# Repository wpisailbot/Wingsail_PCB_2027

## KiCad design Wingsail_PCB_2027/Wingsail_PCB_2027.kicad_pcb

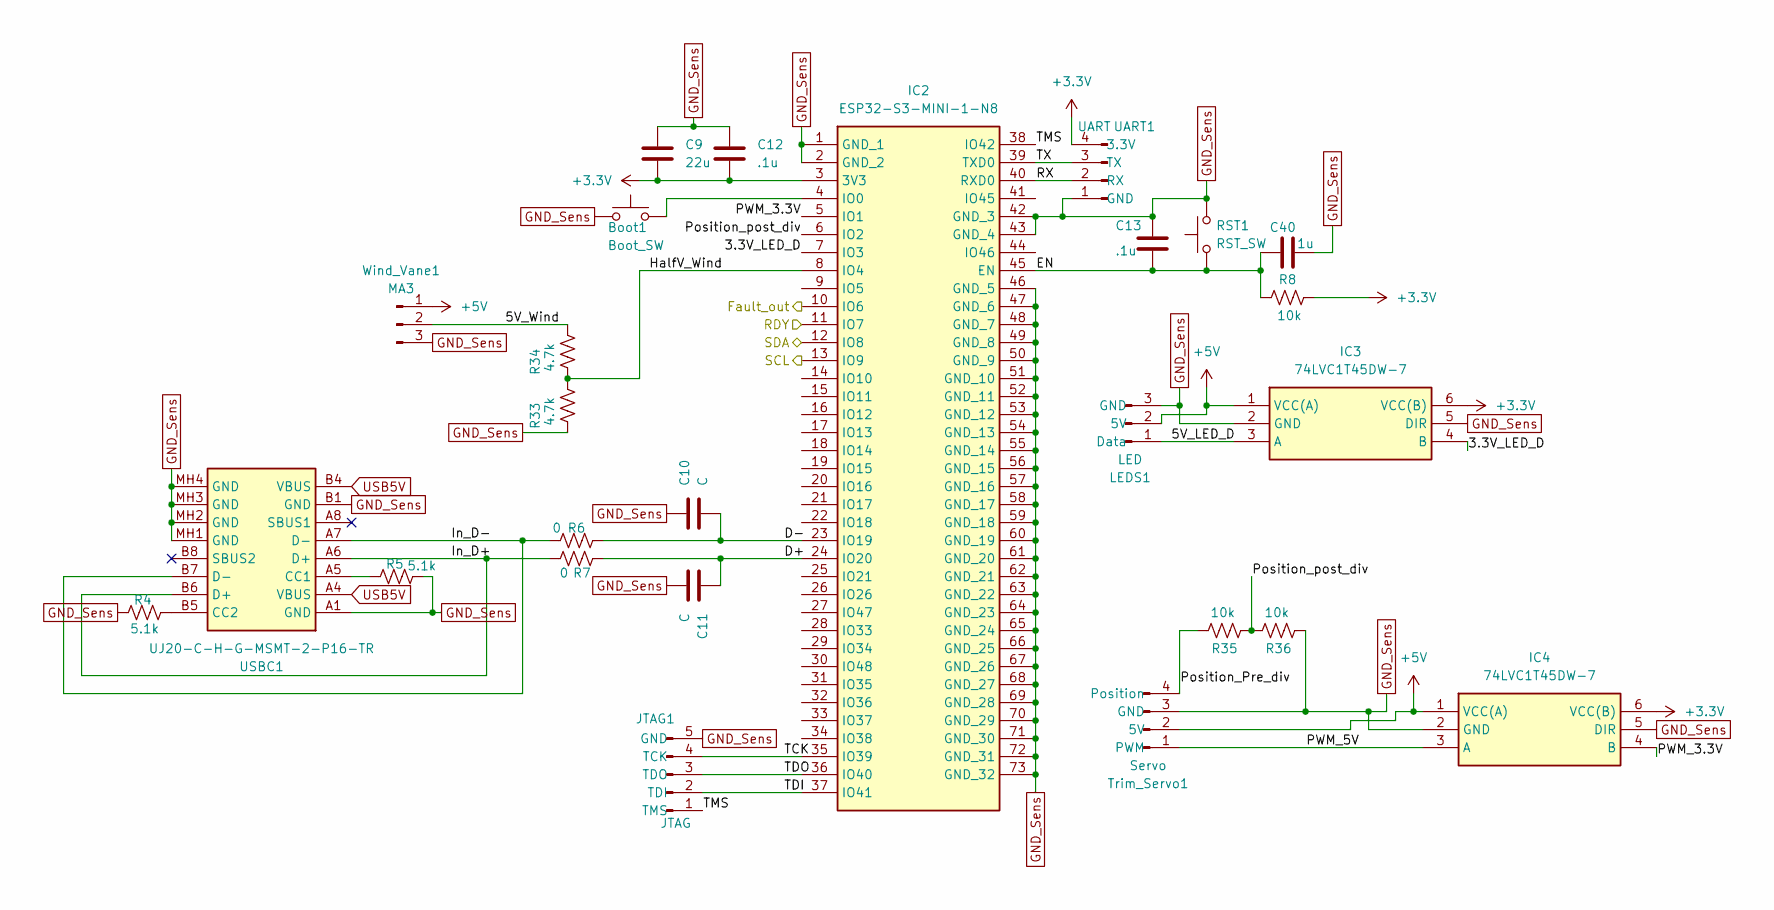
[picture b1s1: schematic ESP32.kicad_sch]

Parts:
Boot1: Boot_SW; PTS636SM43LFS; Part# 1825910-7; Digikey# 450-1804-ND
C9: 22u; C_0805_2012Metric_Pad1.18x1.45mm_HandSolder; Part# CL21A226KQCLRNC; Digikey# 1276-6687-1-ND
C10, C11: C; C_0805_2012Metric_Pad1.18x1.45mm_HandSolder
C12, C13: .1u; C_0805_2012Metric_Pad1.18x1.45mm_HandSolder; Part# CL21B104KBCNNNC; Digikey# 1276-1003-1-ND
C40: 1u; C_0805_2012Metric_Pad1.18x1.45mm_HandSolder; Part# TMK212BBJ106KG-T; Digikey# 587-2985-1-ND
IC2: ESP32-S3-MINI-1-N8; ESP32S3MINI1N8; Manufacturer_Part_Number ESP32-S3-MINI-1-N8; Mouser Part Number 356-ESP32-S3-MINI1N8
IC3, IC4: 74LVC1T45DW-7; SOT65P210X110-6N; Manufacturer_Part_Number 74LVC1T45DW-7; Mouser Part Number 621-74LVC1T45DW-7
JTAG1: JTAG; PinSocket_1x05_P2.54mm_Vertical
LEDS1: LED; JST_XH_B3B-XH-A_1x03_P2.50mm_Vertical
R4, R5: 5.1k; R_0805_2012Metric_Pad1.20x1.40mm_HandSolder; Part# RK73H2ATTD5101F; Digikey# 2019-RK73H2ATTD5101FCT-ND
R6, R7: 0; R_0805_2012Metric_Pad1.20x1.40mm_HandSolder; Part# RMCF0805ZT0R00; Digikey# RMCF0805ZT0R00CT-ND
R8, R35, R36: 10k; R_0805_2012Metric_Pad1.20x1.40mm_HandSolder; Part# RK73H2ATTD1002F; Digikey# 2019-RK73H2ATTD1002FCT-ND
R33, R34: 4.7k; R_0805_2012Metric_Pad1.20x1.40mm_HandSolder; Part# RK73H2ATTD4701F; Digikey# 2019-RK73H2ATTD4701FCT-ND
RST1: RST_SW; PTS636SM43LFS; Part# 1825910-7; Digikey# 450-1804-ND
Trim_Servo1: Servo; JST_XH_B4B-XH-A_1x04_P2.50mm_Vertical
UART1: UART; PinSocket_1x04_P2.54mm_Vertical
USBC1: UJ20-C-H-G-MSMT-2-P16-TR; UJ20CHGMSMT2P16TR; Manufacturer_Part_Number UJ20-C-H-G-MSMT-2-P16-TR; Mouser Part Number 179-UJ20CHGMSMT2P16T
Wind_Vane1: MA3; JST_XH_B3B-XH-A_1x03_P2.50mm_Vertical

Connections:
+3.3V: C9.1, C12.2, IC2.3 (3V3), IC3.6 (VCC(B)), IC4.6 (VCC(B)), R8.2, UART1.4 (3.3V); also elsewhere on the board
+5V: IC3.1 (VCC(A)), IC4.1 (VCC(A)), LEDS1.2 (5V), Trim_Servo1.2 (5V), Wind_Vane1.1; also elsewhere on the board
/BMS/Fault_in: IC2.10 (IO6); also elsewhere on the board
/BMS/RDY: IC2.11 (IO7); also elsewhere on the board
/BMS/SCL: IC2.13 (IO9); also elsewhere on the board
/BMS/SDA: IC2.12 (IO8); also elsewhere on the board
/ESP32/3.3V_LED_D: IC2.7 (IO3), IC3.4 (B)
/ESP32/5V_LED_D: IC3.3 (A), LEDS1.1 (Data)
/ESP32/5V_Wind: R34.2, Wind_Vane1.2
/ESP32/D+: C11.1, IC2.24 (IO20), R7.2
/ESP32/D-: C10.2, IC2.23 (IO19), R6.2
/ESP32/EN: C13.2, C40.1, IC2.45 (EN), R8.1, RST1.1
/ESP32/HalfV_Wind: IC2.8 (IO4), R33.2, R34.1
/ESP32/In_D+: R7.1, USBC1.A6 (D+), USBC1.B6 (D+)
/ESP32/In_D-: R6.1, USBC1.A7 (D-), USBC1.B7 (D-)
/ESP32/PWM_3.3V: IC2.5 (IO1), IC4.4 (B)
/ESP32/PWM_5V: IC4.3 (A), Trim_Servo1.1 (PWM)
/ESP32/Position_Pre_div: R35.2, Trim_Servo1.4 (Position)
/ESP32/Position_post_div: IC2.6 (IO2), R35.1, R36.2
/ESP32/RX: IC2.40 (RXD0), UART1.2 (RX)
/ESP32/TCK: IC2.35 (IO39), JTAG1.4 (TCK)
/ESP32/TDI: IC2.37 (IO41), JTAG1.2 (TDI)
/ESP32/TDO: IC2.36 (IO40), JTAG1.3 (TDO)
/ESP32/TMS: IC2.38 (IO42), JTAG1.1 (TMS)
/ESP32/TX: IC2.39 (TXD0), UART1.3 (TX)
GND_Sens: Boot1.1, C9.2, C10.1, C11.2, C12.1, C13.1, C40.2, IC2.1 (GND_1), IC2.2 (GND_2), IC2.42 (GND_3), IC2.43 (GND_4), IC2.46 (GND_5), IC2.47 (GND_6), IC2.48 (GND_7), IC2.49 (GND_8), IC2.50 (GND_9), IC2.51 (GND_10), IC2.52 (GND_11), IC2.53 (GND_12), IC2.54 (GND_13), IC2.55 (GND_14), IC2.56 (GND_15), IC2.57 (GND_16), IC2.58 (GND_17), IC2.59 (GND_18), IC2.60 (GND_19), IC2.61 (GND_20), IC2.62 (GND_21), IC2.63 (GND_22), IC2.64 (GND_23), IC2.65 (GND_24), IC2.66 (GND_25), IC2.67 (GND_26), IC2.68 (GND_27), IC2.69 (GND_28), IC2.70 (GND_29), IC2.71 (GND_30), IC2.72 (GND_31), IC2.73 (GND_32), IC3.2 (GND), IC3.5 (DIR), IC4.2 (GND), IC4.5 (DIR), JTAG1.5 (GND), LEDS1.3 (GND), R4.1, R5.2, R33.1, R36.1, RST1.2, Trim_Servo1.3 (GND), UART1.1 (GND), USBC1.A1 (GND), USBC1.B1 (GND), USBC1.MH1 (GND), USBC1.MH2 (GND), USBC1.MH3 (GND), USBC1.MH4 (GND), Wind_Vane1.3; also elsewhere on the board
unnamed: Boot1.2, IC2.4 (IO0)
unnamed: R5.1, USBC1.A5 (CC1)
unnamed: R4.2, USBC1.B5 (CC2)
USB5V: USBC1.A4 (VBUS), USBC1.B4 (VBUS); also elsewhere on the board

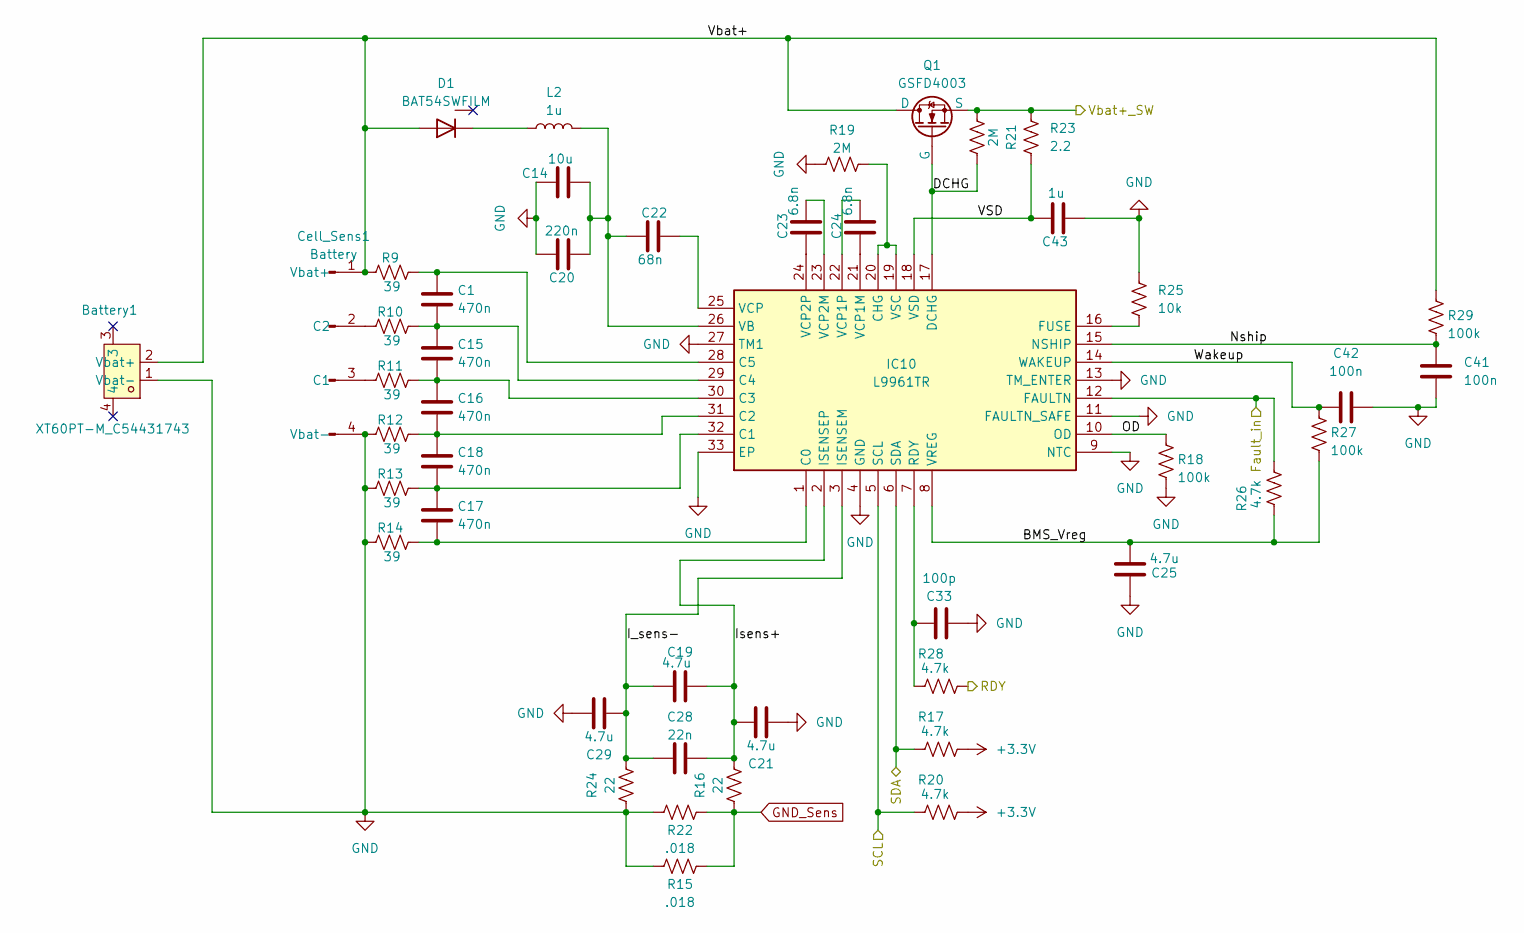
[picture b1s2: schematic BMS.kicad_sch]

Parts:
Battery1: XT60PT-M_C54431743; CONN-SMD_XT60PT-M_C9900188634; MPN XT60PT-M; LCSC Part C54431743
C1, C15, C16, C17, C18: 470n; C_0805_2012Metric_Pad1.18x1.45mm_HandSolder; Part# CL21B474KAFNNNG; Digikey# 1276-6480-1-ND
C14: 10u; C_0805_2012Metric_Pad1.18x1.45mm_HandSolder; Part# TMK212BBJ106KG-T; Digikey# 587-2985-1-ND
C19, C21, C25, C29: 4.7u; C_0805_2012Metric_Pad1.18x1.45mm_HandSolder; Part# GRM219R6YA475KA73D; Digikey# 490-7208-1-ND
C20: 220n; C_0805_2012Metric_Pad1.18x1.45mm_HandSolder; Part# CL21B224KBFNNNF; Digikey# 1276-CL21B224KBFNNNFCT-ND
C22: 68n; C_0805_2012Metric_Pad1.18x1.45mm_HandSolder; Part# GMC21X7R683K50NT; Digikey# 4713-GMC21X7R683K50NTCT-ND
C23, C24: 6.8n; C_0805_2012Metric_Pad1.18x1.45mm_HandSolder; Part# 0805B682K500CT; Digikey# 1292-1587-1-ND
C28: 22n; C_0805_2012Metric_Pad1.18x1.45mm_HandSolder; Part# CL21B223JBANNNC; Digikey# 1276-1826-1-ND
C33: 100p; C_0805_2012Metric_Pad1.18x1.45mm_HandSolder; Part# CL21C101JCANNNC; Digikey# 1276-1261-1-ND
C41, C42: 100n; C_0805_2012Metric_Pad1.18x1.45mm_HandSolder; Part# CL21B104KBCNNNC; Digikey# 1276-1003-1-ND
C43: 1u; C_0805_2012Metric_Pad1.18x1.45mm_HandSolder; Part# TMK212BBJ106KG-T; Digikey# 587-2985-1-ND
Cell_Sens1: Battery; JST_XH_S4B-XH-A_1x04_P2.50mm_Horizontal; Part# S4B-XH-A; Digikey# 455-2243-ND
D1: BAT54SWFILM; SOT-323_SC-70; Part# BAT54SWFILM; Digikey# 497-14153-1-ND
IC10: L9961TR; QFN50P500X500X100-33N-D; Manufacturer_Part_Number L9961TR; Digikey# 497-L9961TRCT-ND
L2: 1u; L_0805_2012Metric_Pad1.05x1.20mm_HandSolder; Part# MLZ2012N1R0LT000; Digikey# 445-6756-1-ND
Q1: GSFD4003; TO-252-GSFD4003; Part# GSFD4003; Digikey# 4786-GSFD4003CT-ND
R9, R10, R11, R12, R13, R14: 39; R_0805_2012Metric_Pad1.20x1.40mm_HandSolder; Power Rating Min 1/8 W; Part# RK73H2ATTD39R0F; Digikey# 2019-RK73H2ATTD39R0FCT-ND
R15, R22: .018; WSHP2818R0180FEA; Part# WSHP2818R0180FEA; Digikey# 541-WSHP2818R0180FEACT-ND
R16, R24: 22; R_0805_2012Metric_Pad1.20x1.40mm_HandSolder; Part# RK73H2ATTD22R0F; Digikey# 2019-RK73H2ATTD22R0FCT-ND
R17, R20, R26, R28: 4.7k; R_0805_2012Metric_Pad1.20x1.40mm_HandSolder; Part# RK73H2ATTD4701F; Digikey# 2019-RK73H2ATTD4701FCT-ND
R18, R27, R29: 100k; R_0805_2012Metric_Pad1.20x1.40mm_HandSolder; Part# RK73H2ATTD1003F; Digikey# 2019-RK73H2ATTD1003FCT-ND
R19, R21: 2M; R_0805_2012Metric_Pad1.20x1.40mm_HandSolder; Part# RK73H2ATTD2004F; Digikey# 2019-RK73H2ATTD2004FCT-ND
R23: 2.2; R_0805_2012Metric_Pad1.20x1.40mm_HandSolder; Part# RK73H2ATTD2R20F; Digikey# 2019-RK73H2ATTD2R20FCT-ND
R25: 10k; R_0805_2012Metric_Pad1.20x1.40mm_HandSolder; Part# RK73H2ATTD1002F; Digikey# 2019-RK73H2ATTD1002FCT-ND

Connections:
+3.3V: R17.2, R20.2; also elsewhere on the board
/BMS/BMS_Vreg: C25.1, IC10.8 (VREG), R26.1, R27.2
/BMS/DCHG: IC10.17 (DCHG), Q1.2 (G), R21.1
/BMS/Fault_in: IC10.12 (FAULTN), R26.2; also elsewhere on the board
/BMS/I_sens-: C19.2, C28.1, C29.1, IC10.3 (ISENSEM), R24.1
/BMS/Isens+: C19.1, C21.2, C28.2, IC10.2 (ISENSEP), R16.1
/BMS/Nship: C41.1, IC10.15 (NSHIP), R29.2
/BMS/OD: IC10.10 (OD), R18.1
/BMS/RDY: R28.2; also elsewhere on the board
/BMS/SCL: IC10.5 (SCL), R20.1; also elsewhere on the board
/BMS/SDA: IC10.6 (SDA), R17.1; also elsewhere on the board
/BMS/VSD: C43.1, IC10.18 (VSD), R23.2
/BMS/Vbat+: Battery1.2 (Vbat+), Cell_Sens1.1 (Vbat+), D1.1 (A), Q1.1 (D), R9.1, R29.1
/BMS/Vbat+_SW: Q1.3 (S), R21.2, R23.1; also elsewhere on the board
/BMS/Wakeup: C42.2, IC10.14 (WAKEUP), R27.1
GND: Battery1.1 (Vbat-), C14.1, C20.1, C21.1, C25.2, C29.2, C33.1, C41.2, C42.1, C43.2, Cell_Sens1.4 (Vbat-), IC10.4 (GND), IC10.9 (NTC), IC10.11 (FAULTN_SAFE), IC10.13 (TM_ENTER), IC10.27 (TM1), IC10.33 (EP), R12.1, R13.1, R14.1, R15.2, R18.2, R19.2, R22.2, R24.2, R25.1
GND_Sens: R15.1, R16.2, R22.1; also elsewhere on the board
unnamed: Cell_Sens1.3 (C1), R11.1
unnamed: Cell_Sens1.2 (C2), R10.1
unnamed: D1.2 (K), L2.1
unnamed: C17.1, IC10.1 (C0), R14.2
unnamed: C17.2, C18.1, IC10.32 (C1), R13.2
unnamed: C16.1, C18.2, IC10.31 (C2), R12.2
unnamed: C15.1, C16.2, IC10.30 (C3), R11.2
unnamed: C1.1, C15.2, IC10.29 (C4), R10.2
unnamed: C1.2, IC10.28 (C5), R9.2
unnamed: IC10.19 (VSC), IC10.20 (CHG), R19.1
unnamed: IC10.16 (FUSE), R25.2
unnamed: C33.2, IC10.7 (RDY), R28.1
unnamed: C14.2, C20.2, C22.2, IC10.26 (VB), L2.2
unnamed: C24.2, IC10.21 (VCP1M)
unnamed: C24.1, IC10.22 (VCP1P)
unnamed: C23.1, IC10.23 (VCP2M)
unnamed: C23.2, IC10.24 (VCP2P)
unnamed: C22.1, IC10.25 (VCP)

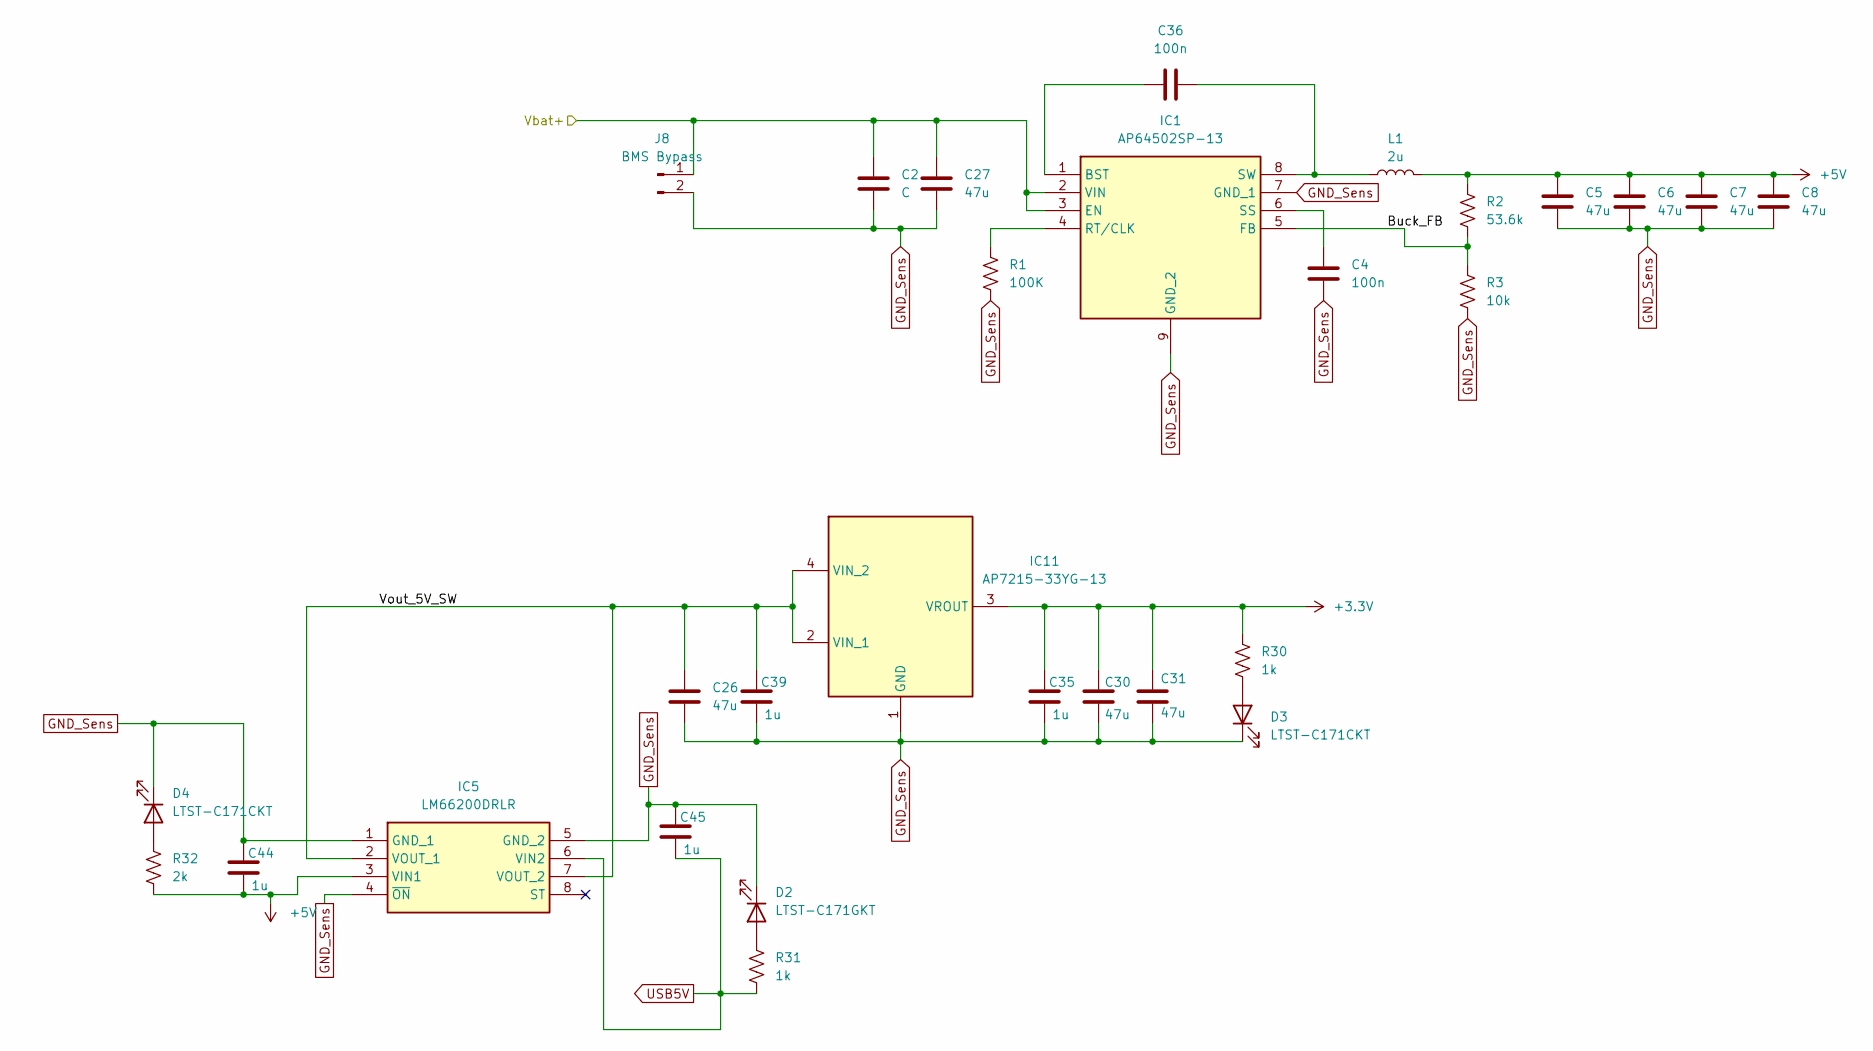
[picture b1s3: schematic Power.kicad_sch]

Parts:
C2: C; C_0805_2012Metric_Pad1.18x1.45mm_HandSolder
C4, C36: 100n; C_0805_2012Metric_Pad1.18x1.45mm_HandSolder; Part# CL21B104KBCNNNC; Digikey# 1276-1003-1-ND
C5, C6, C7, C8, C26, C27, C30, C31: 47u; C_0805_2012Metric_Pad1.18x1.45mm_HandSolder; Part# GRM21BR61A476ME15K; Digikey# 490-GRM21BR61A476ME15KCT-ND
C35, C39, C44, C45: 1u; C_0805_2012Metric_Pad1.18x1.45mm_HandSolder; Part# TMK212BBJ106KG-T; Digikey# 587-2985-1-ND
D2: LTST-C171GKT; LED_0805_2012Metric_Pad1.15x1.40mm_HandSolder
D3, D4: LTST-C171CKT; LED_0805_2012Metric_Pad1.15x1.40mm_HandSolder
IC1: AP64502SP-13; SOIC127P600X163-9N; Manufacturer_Part_Number AP64502SP-13; Mouser Part Number 621-AP64502SP-13
IC5: LM66200DRLR; SOTFL50P160X60-8N; Manufacturer_Part_Number LM66200DRLR; Mouser Part Number 595-LM66200DRLR
IC11: AP7215-33YG-13; AZ7042RTRG1; Manufacturer_Part_Number AP7215-33YG-13; Mouser Part Number 621-AP7215-33YG-13
J8: BMS Bypass; PinHeader_1x02_P2.54mm_Vertical
L1: 2u; IND-SMD_L7.1-W6.6; Part# CSBX0650-2R0M; Digikey# 4044-CSBX0650-2R0MCT-ND
R1: 100K; R_0805_2012Metric_Pad1.20x1.40mm_HandSolder; Part# RK73H2ATTD1003F; Digikey# 2019-RK73H2ATTD1003FCT-ND
R2: 53.6k; R_0805_2012Metric_Pad1.20x1.40mm_HandSolder; Part# RK73H2ATTD5362F; Digikey# 2019-RK73H2ATTD5362FCT-ND
R3: 10k; R_0805_2012Metric_Pad1.20x1.40mm_HandSolder; Part# RK73H2ATTD1002F; Digikey# 2019-RK73H2ATTD1002FCT-ND
R30, R31: 1k; R_0805_2012Metric_Pad1.20x1.40mm_HandSolder; Part# RK73H2ATTD1001F; Digikey# 2019-RK73H2ATTD1001FCT-ND
R32: 2k; R_0805_2012Metric_Pad1.20x1.40mm_HandSolder; Part# RK73H2ATTD2001F; Digikey# 2019-RK73H2ATTD2001FCT-ND

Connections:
+3.3V: C30.1, C31.1, C35.1, IC11.3 (VROUT), R30.1; also elsewhere on the board
+5V: C5.1, C6.1, C7.1, C8.1, C44.2, IC5.3 (VIN1), L1.2, R2.1, R32.2; also elsewhere on the board
/BMS/Vbat+_SW: C2.1, C27.1, IC1.2 (VIN), IC1.3 (EN), J8.1; also elsewhere on the board
/Power/Buck_FB: IC1.5 (FB), R2.2, R3.1
/Power/Vout_5V_SW: C26.1, C39.1, IC5.2 (VOUT_1), IC5.7 (VOUT_2), IC11.2 (VIN_1), IC11.4 (VIN_2)
GND_Sens: C2.2, C4.1, C5.2, C6.2, C7.2, C8.2, C26.2, C27.2, C30.2, C31.2, C35.2, C39.2, C44.1, C45.1, D2.1 (K), D3.1 (K), D4.1 (K), IC1.7 (GND_1), IC1.9 (GND_2), IC5.1 (GND_1), IC5.4 (~ON), IC5.5 (GND_2), IC11.1 (GND), J8.2, R1.2, R3.2; also elsewhere on the board
unnamed: D2.2 (A), R31.1
unnamed: D3.2 (A), R30.2
unnamed: D4.2 (A), R32.1
unnamed: C36.2, IC1.1 (BST)
unnamed: IC1.4 (RT/CLK), R1.1
unnamed: C4.2, IC1.6 (SS)
unnamed: C36.1, IC1.8 (SW), L1.1
USB5V: C45.2, IC5.6 (VIN2), R31.2; also elsewhere on the board

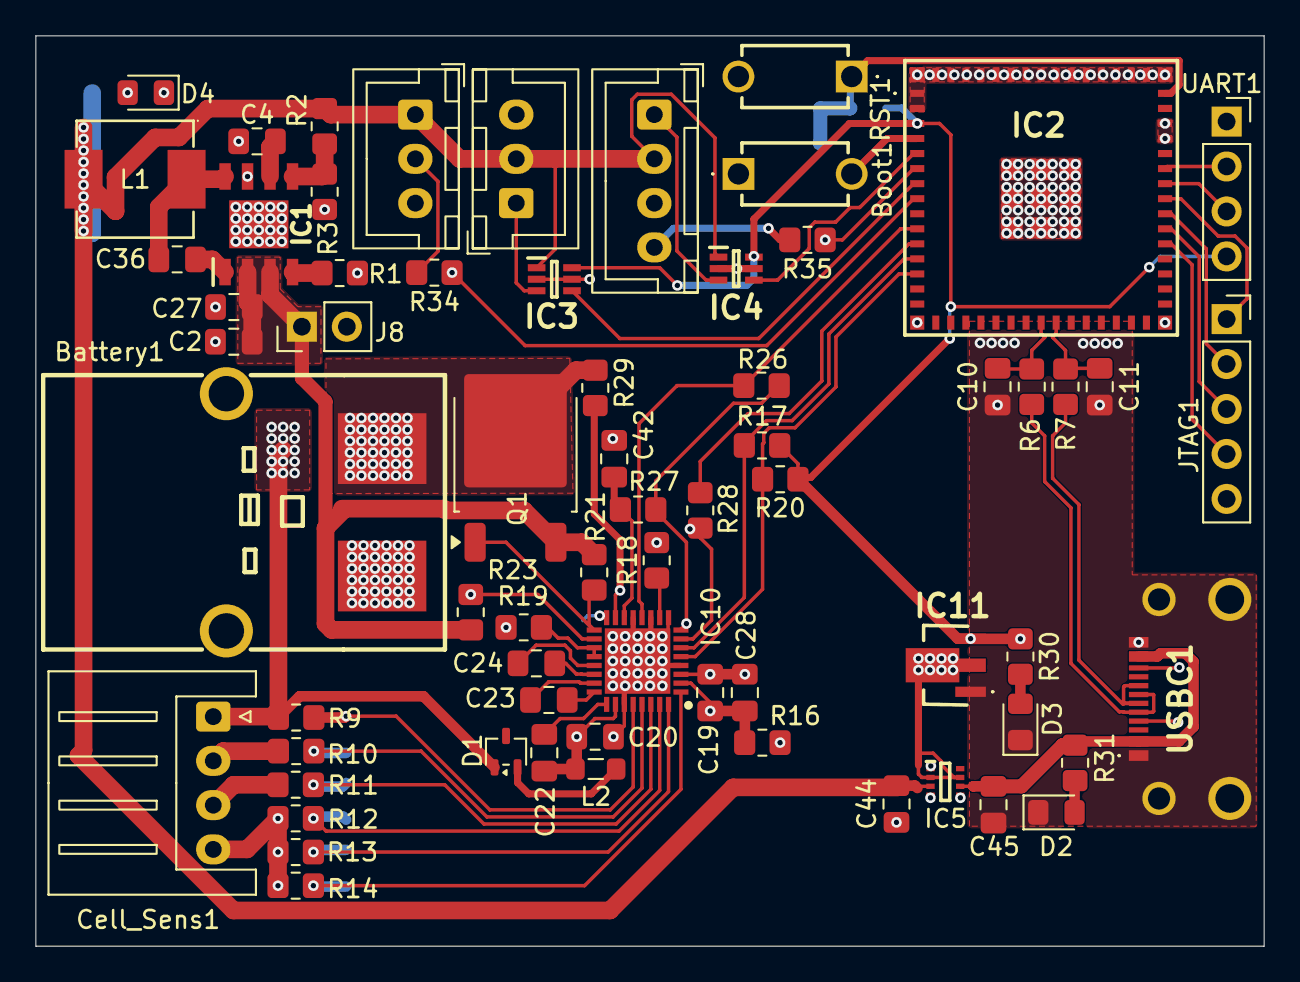
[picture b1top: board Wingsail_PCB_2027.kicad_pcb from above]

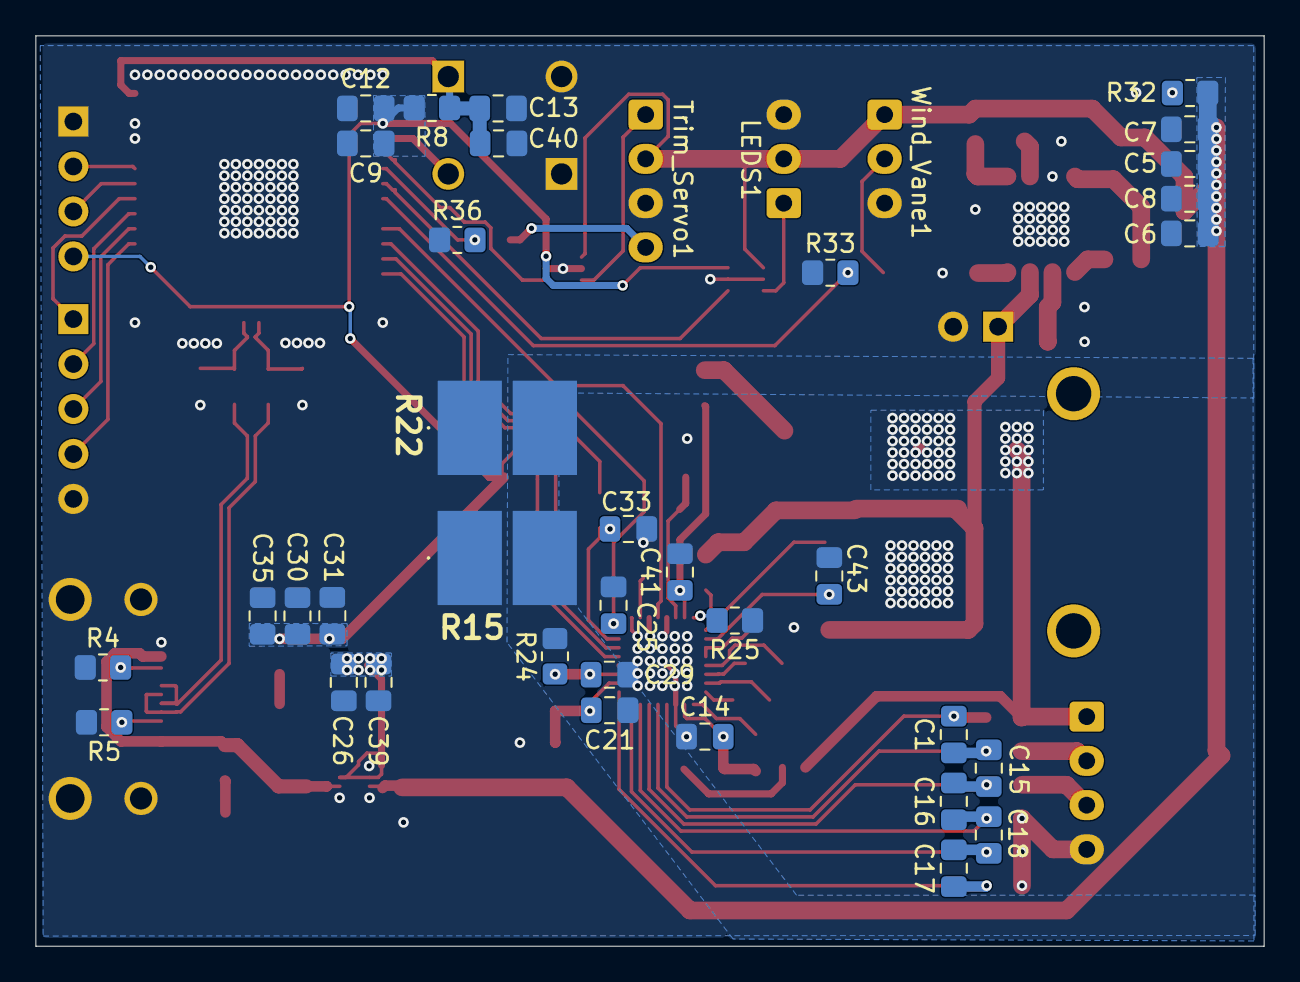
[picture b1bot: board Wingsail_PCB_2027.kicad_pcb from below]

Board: 2 copper layers, 69.4 x 51.4 mm, 101 parts (35 on the bottom side), 68 nets.
